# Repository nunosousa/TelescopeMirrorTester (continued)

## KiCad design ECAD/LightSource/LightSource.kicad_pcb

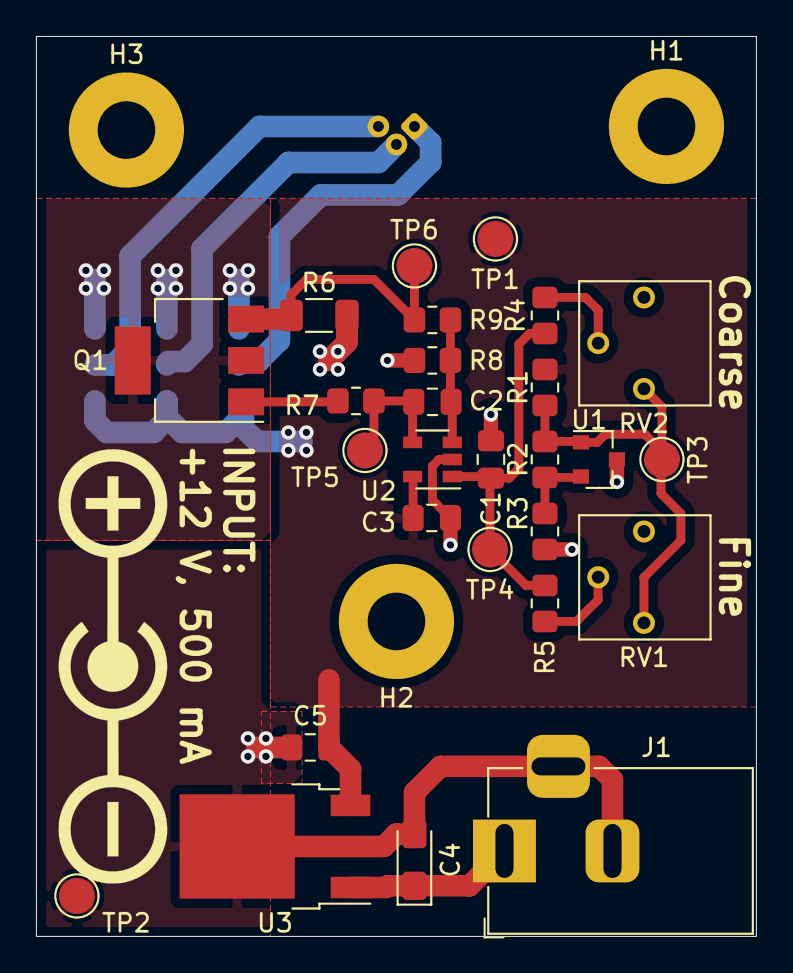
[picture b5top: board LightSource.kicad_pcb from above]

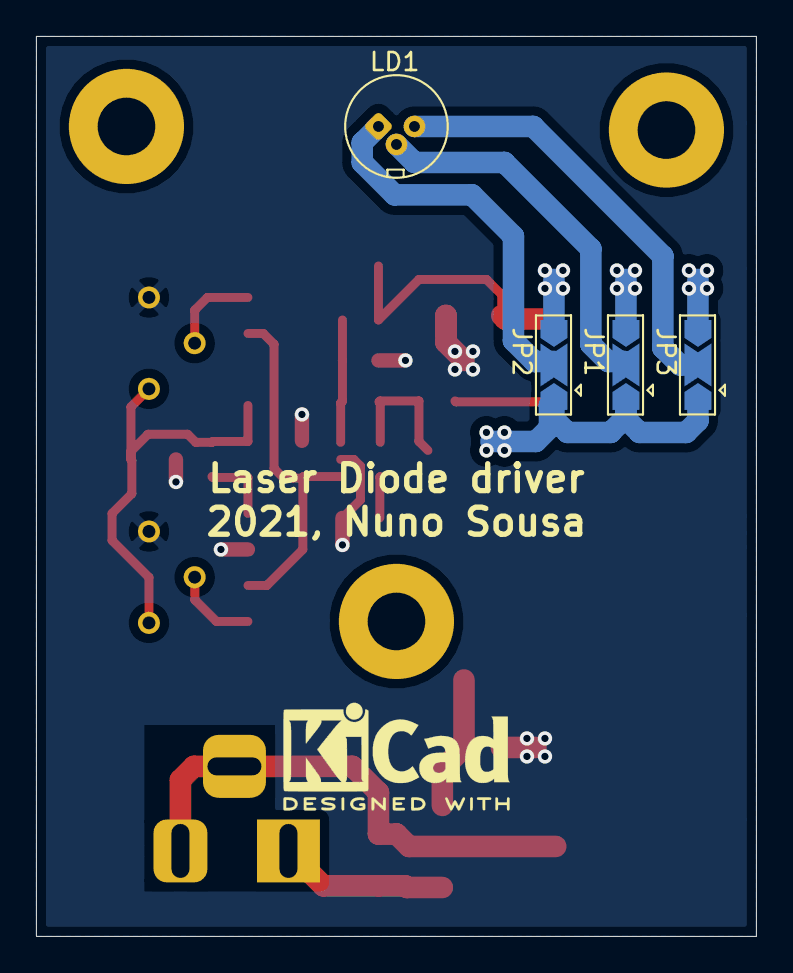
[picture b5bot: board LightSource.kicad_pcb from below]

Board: 2 copper layers, 40.0 x 50.0 mm, 34 parts (4 on the bottom side), 16 nets.

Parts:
C1: 10uC; C_0805_2012Metric_Pad1.18x1.45mm_HandSolder
C2: 100pC; C_0805_2012Metric_Pad1.18x1.45mm_HandSolder
C3, C5: 0.1uC; C_0805_2012Metric_Pad1.18x1.45mm_HandSolder
C4: 0.33uCP; CP_EIA-3216-18_Kemet-A_Pad1.58x1.35mm_HandSolder
H1, H2, H3: MountingHole; MountingHole_3.2mm_M3_Pad
J1: Barrel_Jack_Switch; BarrelJack_Horizontal
JP1, JP2, JP3: JP; SolderJumper-3_P2.0mm_Open_TrianglePad1.0x1.5mm
LD1: LD; LaserDiode_TO18-D5.6-3
Q1: FZT694BTA; SOT-223-3_TabPin2
R1: 510R; R_0805_2012Metric_Pad1.20x1.40mm_HandSolder
R2, R7: 0R; R_0805_2012Metric_Pad1.20x1.40mm_HandSolder
R3: NC; R_0805_2012Metric_Pad1.20x1.40mm_HandSolder
R4: 10kR; R_0805_2012Metric_Pad1.20x1.40mm_HandSolder
R5: 100kR; R_0805_2012Metric_Pad1.20x1.40mm_HandSolder
R6: 120R; R_1206_3216Metric_Pad1.30x1.75mm_HandSolder
R8: 15kR; R_0805_2012Metric_Pad1.20x1.40mm_HandSolder
R9: 30kR; R_0805_2012Metric_Pad1.20x1.40mm_HandSolder
RV1, RV2: 500R; Potentiometer_Bourns_3362P_Vertical
TP1, TP2, TP3, TP4, TP5, TP6: TestPoint; TestPoint_Pad_D2.0mm
U1: TL431; SOT-23
U2: LM321; SOT-23-5
U3: L78M09; TO-252-2

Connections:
+9V: C3.1, C5.1, JP1.1, JP2.1, JP3.1, R1.1, TP1.1, U2.5, U3.3
+12V: C4.1, J1.1, U3.1
/Light Source/Cathode: JP1.3, JP2.3, JP3.3, Q1.2
/Vout: R1.2, R2.1, RV1.1, RV2.1, TP3.1, U1.1
/Vref: R2.2, R3.1, U1.2
GND: C1.2, C3.2, C4.2, C5.2, J1.2, J1.3, R3.2, R6.2, R8.2, RV1.3, RV2.3, TP2.1, U1.3, U2.2, U3.2
unnamed: C1.1, R4.1, R5.1, TP4.1, U2.1
unnamed: C2.1, R7.2, TP5.1, U2.4
unnamed: C2.2, R8.1, R9.2, U2.3
unnamed: JP1.2, LD1.2
unnamed: JP2.2, LD1.1
unnamed: JP3.2, LD1.3
unnamed: Q1.1, R7.1
unnamed: Q1.3, R6.1, R9.1, TP6.1
unnamed: R4.2, RV2.2
unnamed: R5.2, RV1.2

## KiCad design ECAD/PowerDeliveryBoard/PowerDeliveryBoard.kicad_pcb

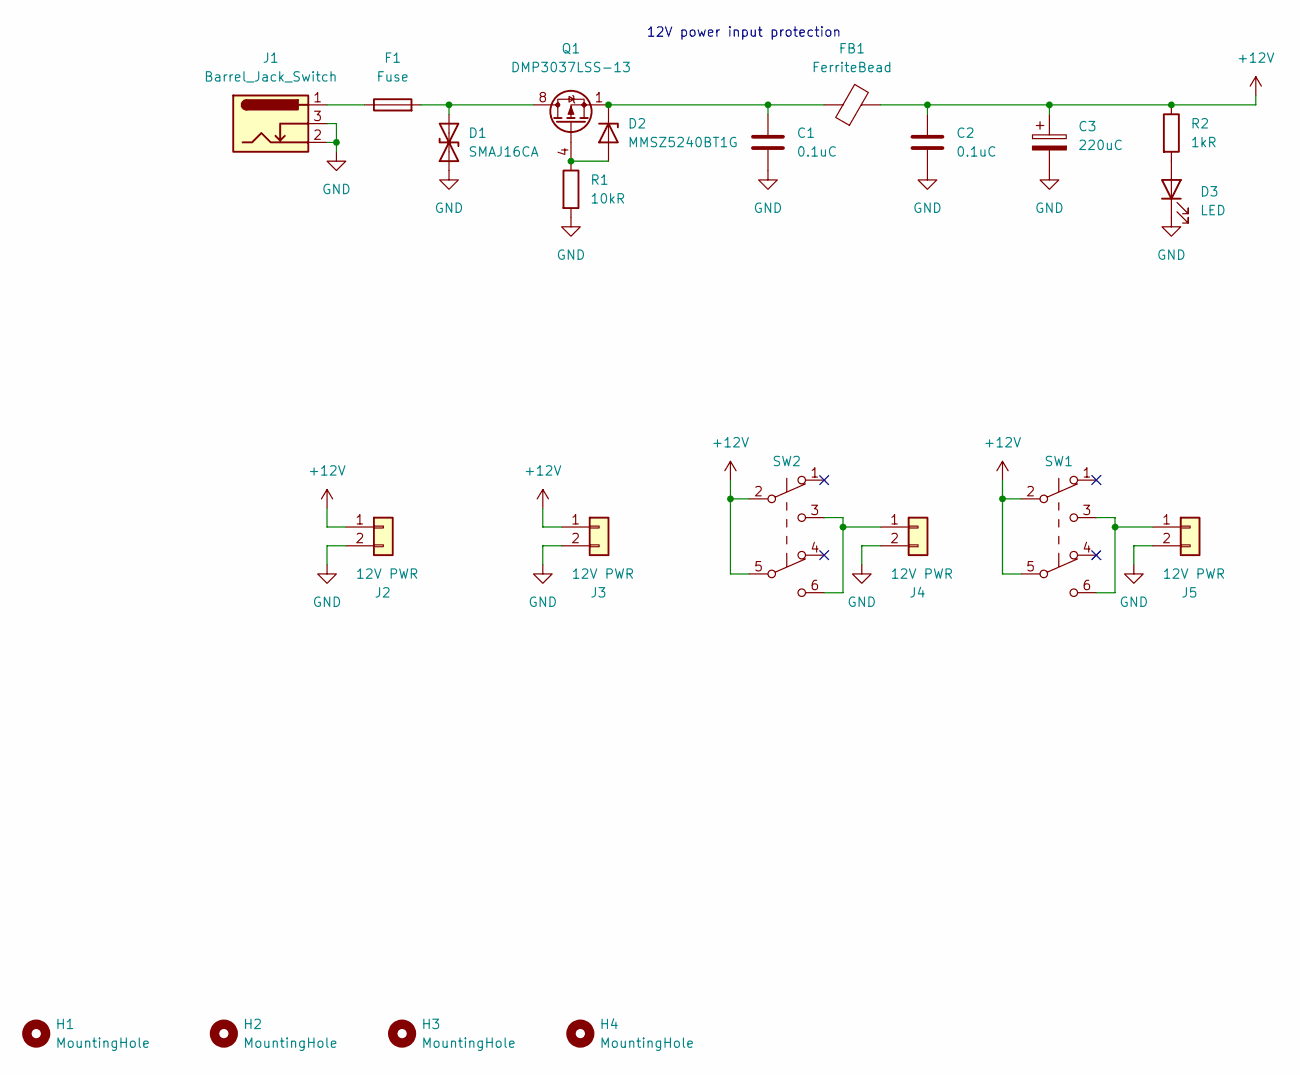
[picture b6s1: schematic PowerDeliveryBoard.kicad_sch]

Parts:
C1, C2: 0.1uC; C_0805_2012Metric_Pad1.18x1.45mm_HandSolder; MPN CL21B104KBCNNNC
C3: 220uC; CP_Radial_D8.0mm_P3.50mm; MPN 25YXF220MEFC8X11.5
D1: SMAJ16CA; D_SMA; MPN SMAJ16CA-13-F
D2: MMSZ5240BT1G; D_SOD-123; MPN MMSZ5240BT1G
D3: LED; D_0805_2012Metric_Pad1.15x1.40mm_HandSolder; MPN 17-21SYGC/S530-E3/TR8
F1: Fuse; Fuseholder_Cylinder-5x20mm_Stelvio-Kontek_PTF78_Horizontal_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; MPN PTF-77
FB1: FerriteBead; L_1806_4516Metric; MPN BLM41PG600SN1L
H1, H2, H3, H4: MountingHole; MountingHole_5.3mm_M5; MPN N/A
J1: Barrel_Jack_Switch; BarrelJack_DC-042C-W-2.5_Horizontal; MPN DC-042C-W-2.5
J2, J3, J4, J5: 12V PWR; HC-2510-2A; MPN HC-2510-2A
Q1: DMP3037LSS-13; SOIC-8_3.9x4.9mm_P1.27mm; MPN DMP3037LSS-13
R1: 10kR; R_0805_2012Metric_Pad1.20x1.40mm_HandSolder; MPN RC0805FR-0710KL
R2: 1kR; R_0805_2012Metric_Pad1.20x1.40mm_HandSolder; MPN AC0805FR-7W1KL
SW1, SW2: SW_Push_DPDT; SW_Push_2P2T_Toggle_Generic_5_8_x_5_8; MPN PB22E60L

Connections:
+12V: C2.2, C3.1, FB1.2, J2.1, J3.1, R2.1, SW1.2 (B), SW1.5 (B), SW2.2 (B), SW2.5 (B)
GND: C1.1, C2.1, C3.2, D1.1 (A1), D3.1 (K), J1.2, J1.3, J2.2, J3.2, J4.2, J5.2, R1.2
unnamed: C1.2, D2.1 (K), FB1.1, Q1.1 (S), Q1.2 (S), Q1.3 (S)
unnamed: D1.2 (A2), F1.2, Q1.5 (D), Q1.6 (D), Q1.7 (D), Q1.8 (D)
unnamed: D2.2 (A), Q1.4 (G), R1.1
unnamed: F1.1, J1.1
unnamed: J4.1, SW2.3 (C), SW2.6 (C)
unnamed: J5.1, SW1.3 (C), SW1.6 (C)
unnamed: D3.2 (A), R2.2

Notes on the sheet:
12V power input protection

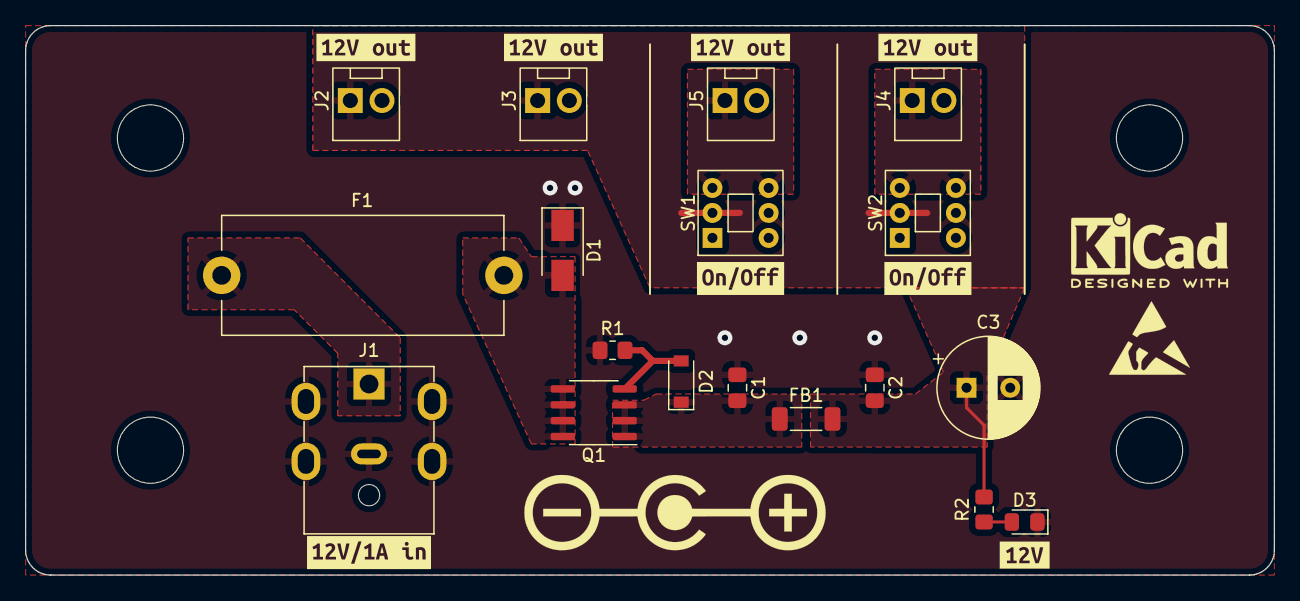
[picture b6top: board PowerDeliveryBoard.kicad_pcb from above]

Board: 2 copper layers, 100.0 x 44.0 mm, 30 parts (0 on the bottom side), 9 nets.

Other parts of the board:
kibuzzard-6388F516: G***; kibuzzard-6388F516
kibuzzard-63891CDB: G***; kibuzzard-63891CDB
kibuzzard-638910D3, kibuzzard-638910D3#2: G***; kibuzzard-638910D3
kibuzzard-638911E5: G***; kibuzzard-638911E5
kibuzzard-638911EA: G***; kibuzzard-638911EA
kibuzzard-6389104C, kibuzzard-6389104C#2: G***; kibuzzard-6389104C

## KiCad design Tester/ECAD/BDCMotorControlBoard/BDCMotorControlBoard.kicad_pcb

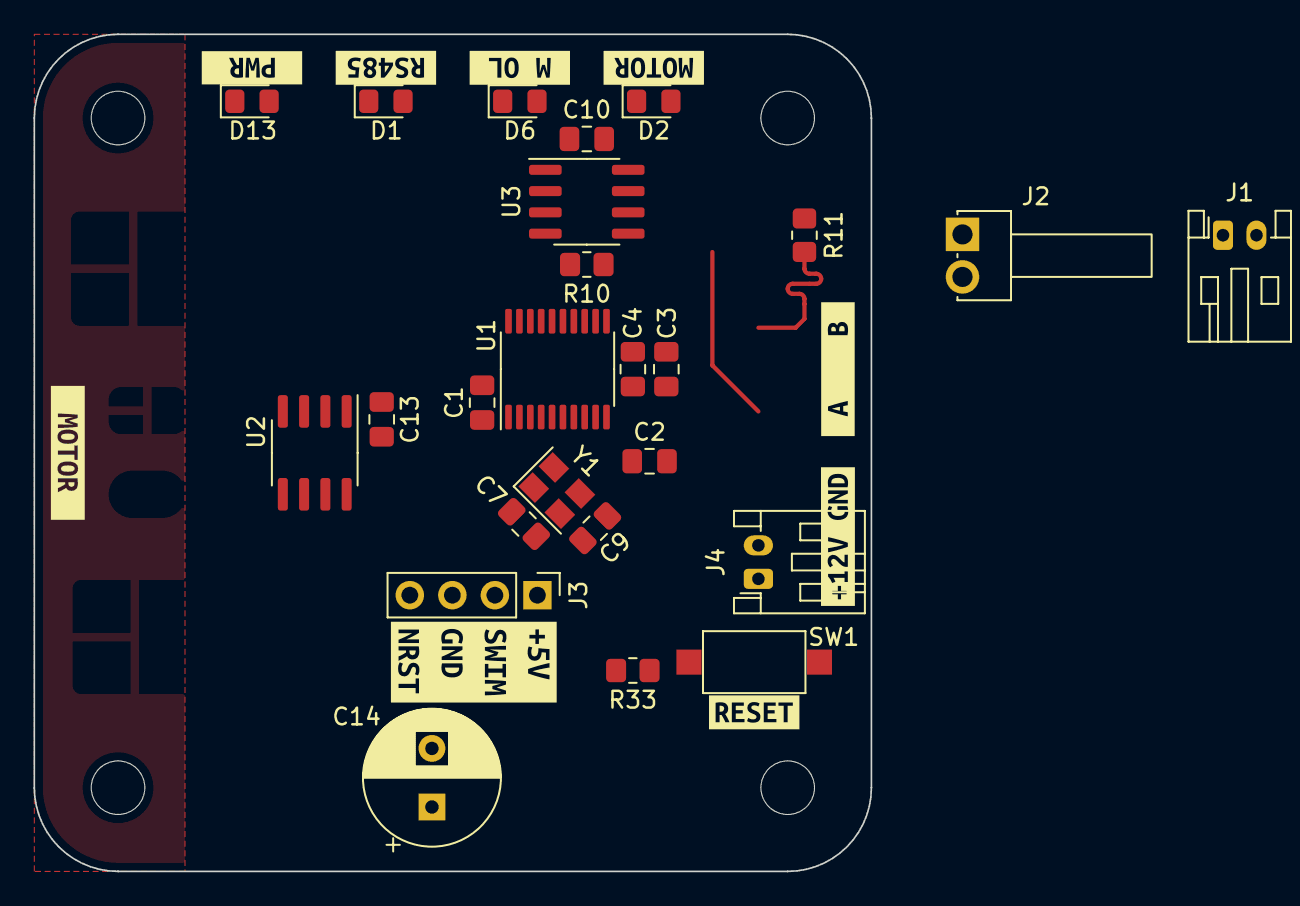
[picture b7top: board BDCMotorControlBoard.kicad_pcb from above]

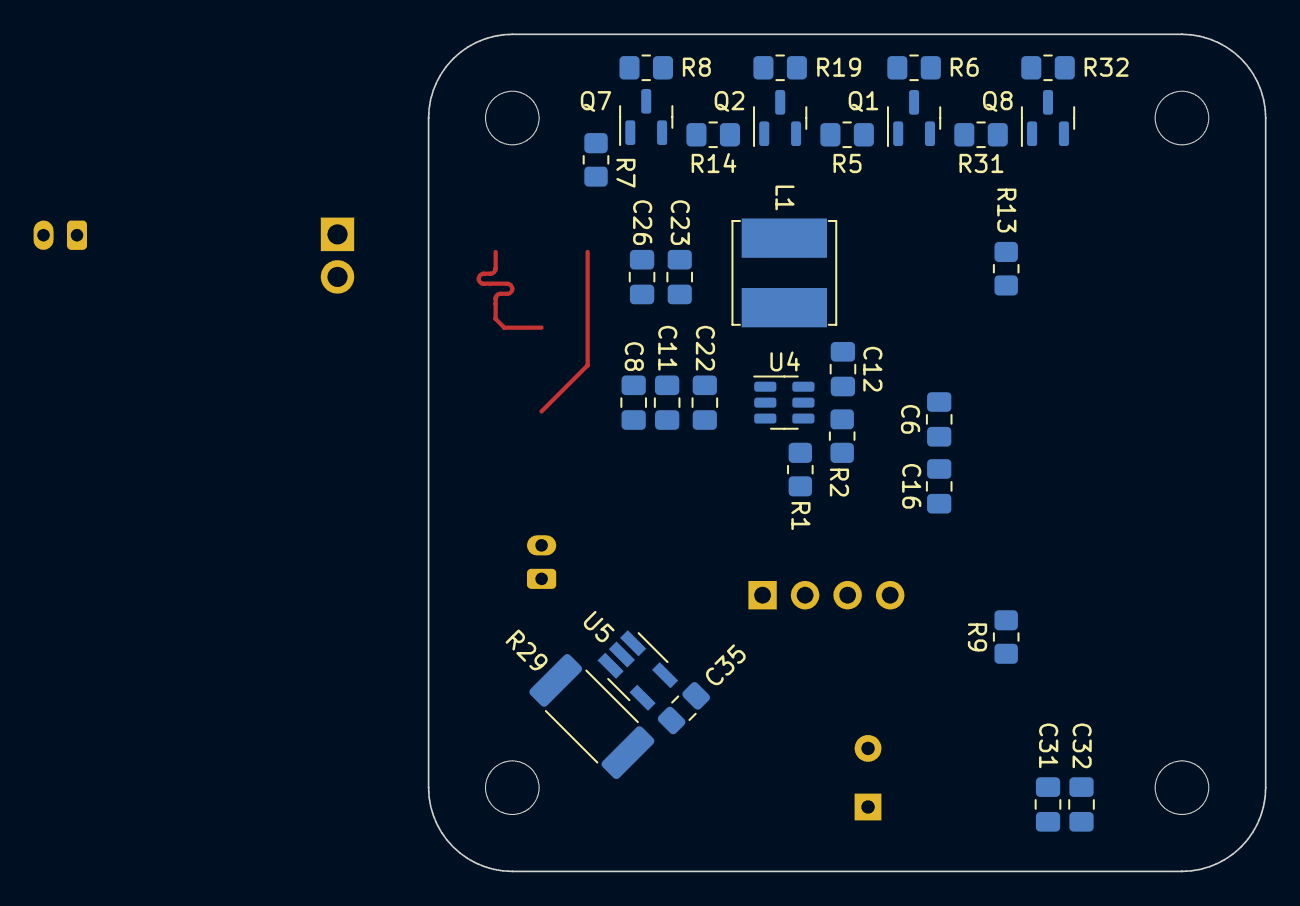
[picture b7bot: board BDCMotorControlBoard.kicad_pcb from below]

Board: 4 copper layers, 50.0 x 50.0 mm, 69 parts (31 on the bottom side), 34 nets.

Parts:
C1, C3, C10, C12, C22, C35: 0.1uC; C_0805_2012Metric_Pad1.18x1.45mm_HandSolder
C2, C4, C6, C13, C16, C31, C32: 1uC; C_0805_2012Metric_Pad1.18x1.45mm_HandSolder
C7, C9: 12pC; C_0805_2012Metric_Pad1.18x1.45mm_HandSolder
C8, C11: 10uC; C_0805_2012Metric_Pad1.18x1.45mm_HandSolder
C14: 220uC; CP_Radial_D8.0mm_P3.50mm
C23, C26: 22uC; C_0805_2012Metric_Pad1.18x1.45mm_HandSolder
D1, D2, D6, D13: LED; LED_0805_2012Metric_Pad1.15x1.40mm_HandSolder
H1, H2, H3, H4: MountingHole; MountingHole_3.2mm_M3
J1: RS485; JST_PH_S2B-PH-K_1x02_P2.00mm_Horizontal
J2: 12V PWR; HC-2510-2AW
J3: SWIM connector; PinHeader_1x04_P2.54mm_Vertical
J4: Motor; JST_PH_S2B-PH-K_1x02_P2.00mm_Horizontal
L1: 3.3uL; L_Bourns_SRN6045TA
Q1, Q2, Q7, Q8: 2N7002; SOT-23
R1, R9, R10, R13, R33: 10kR; R_0805_2012Metric_Pad1.20x1.40mm_HandSolder
R2: 54.9kR; R_0805_2012Metric_Pad1.20x1.40mm_HandSolder
R5, R7, R14, R31: 10R; R_0805_2012Metric_Pad1.20x1.40mm_HandSolder
R6, R8, R19, R32: 150R; R_0805_2012Metric_Pad1.20x1.40mm_HandSolder
R11: 120R; R_0805_2012Metric_Pad1.20x1.40mm_HandSolder
R29: 20mR; R_2512_6332Metric_Pad1.40x3.35mm_HandSolder
SW1: SW_Push; SW_SPST_CK_RS282G05A3
U1: STM8S003F3P6; TSSOP-20_4.4x6.5mm_P0.65mm
U2: ZXBM5210-S; SOIC-8_3.9x4.9mm_P1.27mm
U3: SP485; SOIC-8_3.9x4.9mm_P1.27mm
U4: TPS563201; SOT-23-6
U5: INA180A2; SOT-23-5_HandSoldering
Y1: Crystal_GND24; Crystal_SMD_3225-4Pin_3.2x2.5mm
kibuzzard-633AA34D: G***; kibuzzard-633AA34D
kibuzzard-634C1717: G***; kibuzzard-634C1717
kibuzzard-6349C15E: G***; kibuzzard-6349C15E
kibuzzard-6349C16E: G***; kibuzzard-6349C16E
kibuzzard-6349C164: G***; kibuzzard-6349C164
kibuzzard-6349C168: G***; kibuzzard-6349C168
kibuzzard-63377EA3: G***; kibuzzard-63377EA3
kibuzzard-63377ED3: G***; kibuzzard-63377ED3
kibuzzard-633802D7: G***; kibuzzard-633802D7

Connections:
+5V: C3.1, C4.1, C10.1, C23.1, C26.1, C35.1, J3.1, L1.2, R2.2, R6.1, R8.1, R19.1, R32.1, R33.1, U1.9 (VDD), U3.8 (VCC), U5.5 (V+)
+12V: C8.1, C11.1, C22.1, J2.1, R29.1, U4.3 (VIN), U4.5 (EN), U5.3 (+)
/A_Meas: U1.19 (PD2), U5.1
/H-bridge/Top_Rail: C6.1, C14.1, C16.1, C31.1, C32.1, R9.1, R29.2, U5.4 (-)
/M_ACT_LED: R7.1, U1.17 (PC7)
/NRST: C1.1, J3.4, R33.2, SW1.1, U1.4 (NRST)
/OC_LED: R14.1, U1.12 (PB4)
/OSCIN: C7.1, U1.5 (PA1), Y1.1
/OSCOUT: C9.1, U1.6 (PA2), Y1.3
/PWR_LED: R31.1, U1.10 (PA3)
/RS485_DI: U1.2 (PD5), U3.4 (DI)
/RS485_LED: R5.1, U1.20 (PD3)
/RS485_RO: U1.3 (PD6), U3.1 (RO)
/RS485_TX: R10.1, U1.1 (PD4), U3.2 (~RE), U3.3 (DE)
/SWIM: J3.2, U1.18 (PD1)
GND: C1.2, C2.2, C3.2, C4.2, C6.2, C7.2, C8.2, C9.2, C10.2, C11.2, C13.2, C14.2, C16.2, C22.2, C23.2, C26.2, C31.2, C32.2, C35.2, J2.2, J3.3, Q1.2 (S), Q2.2 (S), Q7.2 (S), Q8.2 (S), R1.2, R10.2, R13.2, SW1.2, U1.7 (VSS), U3.5 (GND), U4.1 (GND), U5.2 (GND), Y1.2, Y1.4
unnamed: C2.1, U1.8 (VCAP)
unnamed: C12.1, U4.6 (VBST)
unnamed: C12.2, L1.1, U4.2 (SW)
unnamed: D1.1 (K), Q1.3 (D)
unnamed: D1.2 (A), R6.2
unnamed: D2.1 (K), Q7.3 (D)
unnamed: D2.2 (A), R8.2
unnamed: D6.1 (K), Q2.3 (D)
unnamed: D6.2 (A), R19.2
unnamed: D13.1 (K), Q8.3 (D)
unnamed: D13.2 (A), R32.2
unnamed: J1.1, R11.1, U3.7 (B)
unnamed: J1.2, R11.2, U3.6 (A)
unnamed: Q1.1 (G), R5.2
unnamed: Q2.1 (G), R14.2
unnamed: Q7.1 (G), R7.2
unnamed: Q8.1 (G), R31.2
unnamed: R1.1, R2.1, U4.4 (VFB)

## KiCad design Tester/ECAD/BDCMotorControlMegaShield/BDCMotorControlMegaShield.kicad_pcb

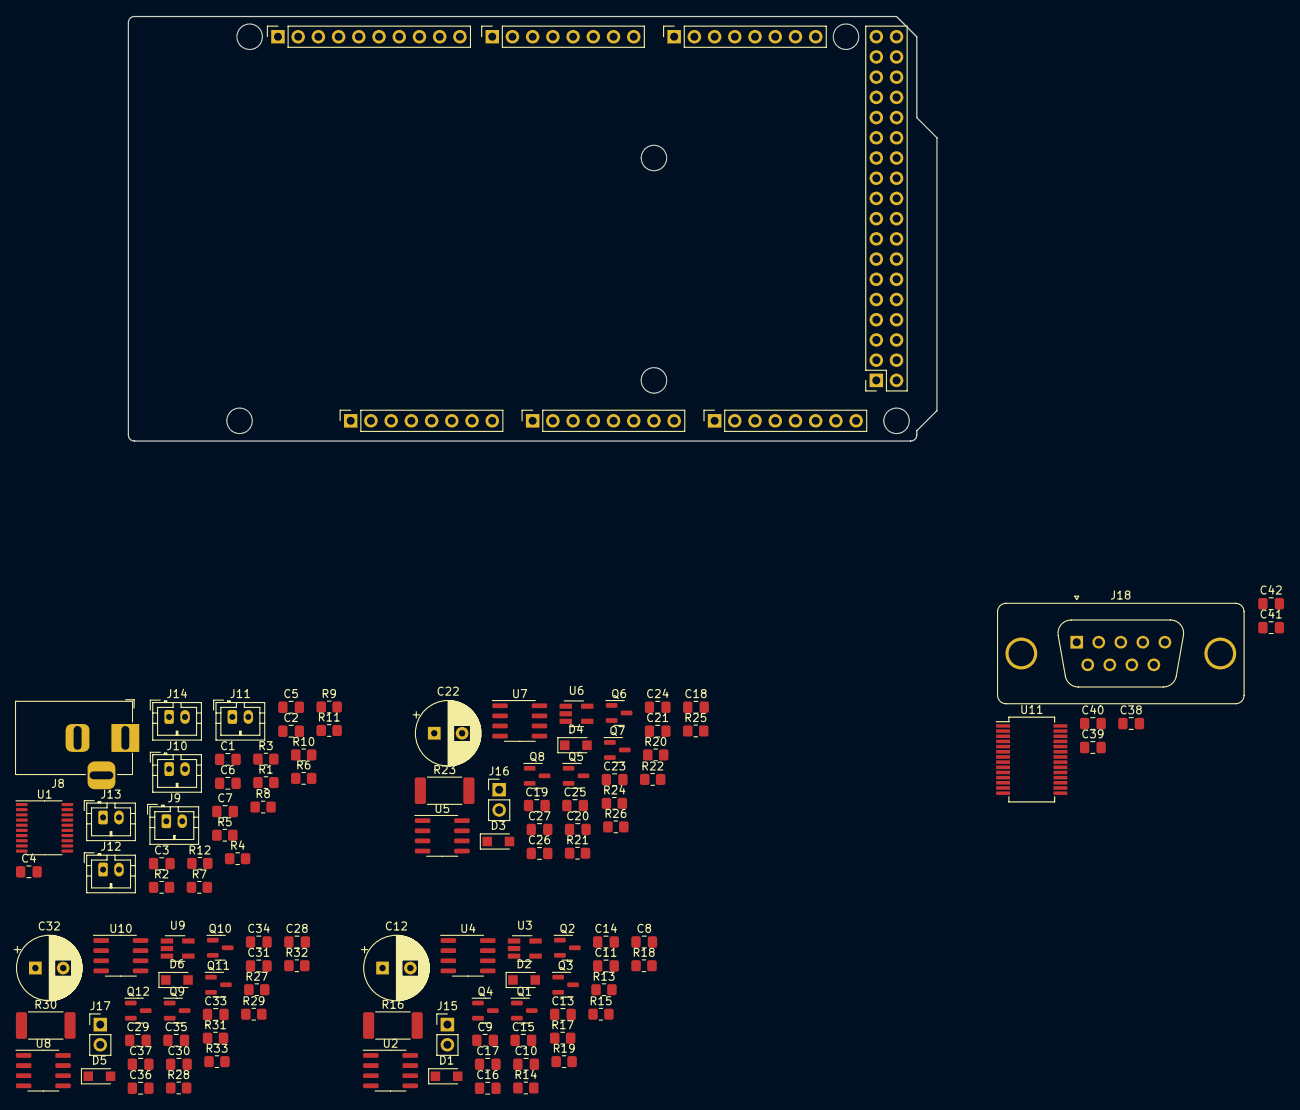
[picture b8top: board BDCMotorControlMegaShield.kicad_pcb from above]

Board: 2 copper layers, 101.6 x 53.3 mm, 128 parts (0 on the bottom side), 86 nets, no tracks yet.

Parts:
C1, C2, C3, C4, C5, C6, C9, C15, C16, C19, C25, C26, C29, C35, C36, C38, C39, C40, C41, C42: 0.1uC; C_0805_2012Metric_Pad1.18x1.45mm_HandSolder
C7, C8, C10, C11, C13, C14, C17, C18, C20, C21, C23, C24, C27, C28, C30, C31, C33, C34, C37: 1uC; C_0805_2012Metric_Pad1.18x1.45mm_HandSolder
C12, C22, C32: 220uC; CP_Radial_D8.0mm_P3.50mm
D1, D2, D3, D4, D5, D6: PMEG6010ER; Nexperia_CFP3_SOD-123W
J1: Power; PinSocket_1x08_P2.54mm_Vertical
J2: PWM; PinSocket_1x10_P2.54mm_Vertical
J3, J5: Analog; PinSocket_1x08_P2.54mm_Vertical
J4: PWM; PinSocket_1x08_P2.54mm_Vertical
J6: Communication; PinSocket_1x08_P2.54mm_Vertical
J7: Digital; PinSocket_2x18_P2.54mm_Vertical
J8: Barrel_Jack_Switch; BarrelJack_Horizontal
J9, J10: SW0 switch; JST_PH_B2B-PH-K_1x02_P2.00mm_Vertical
J11, J12, J13, J14: SW1 switch; JST_PH_B2B-PH-K_1x02_P2.00mm_Vertical
J15, J16, J17: Motor connector; PinHeader_1x02_P2.54mm_Vertical
J18: DB9_Male; DSUB-9_Male_Vertical_P2.77x2.84mm_MountingHoles
MH1, MH2, MH3, MH4, MH5, MH6: MountingHole_3.2mm
Q1, Q2, Q3, Q4, Q5, Q6, Q7, Q8, Q9, Q10, Q11, Q12: Q_NMOS_GSD; SOT-23
R1, R2, R3, R4, R5, R6, R7, R8, R9, R10, R11, R12: 10kR; R_0805_2012Metric_Pad1.20x1.40mm_HandSolder
R13, R14, R15, R17, R18, R19, R20, R21, R22, R24, R25, R26, R27, R28, R29, R31, R32, R33: 10R; R_0805_2012Metric_Pad1.20x1.40mm_HandSolder
R16, R23, R30: 20mR; R_2512_6332Metric_Pad1.40x3.35mm_HandSolder
U1: 74HC7541; TSSOP-20_4.4x6.5mm_P0.65mm
U2, U4, U5, U7, U8, U10: IR2103; SOIC-8_3.9x4.9mm_P1.27mm
U3, U6, U9: INA180A2; SOT-23-5_HandSoldering
U11: SP213E; SSOP-28_5.3x10.2mm_P0.65mm

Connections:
+5V: C7.1, C16.1, C26.1, C36.1, J1.5, J7.35, J7.36, R1.1, R2.1, R3.1, R4.1, R5.1, R6.1, U1.20 (VCC), U3.5 (V+), U6.5 (V+), U9.5 (V+)
+12V: J8.1, R16.2, R23.2, R30.2, U3.3 (+), U6.3 (+), U9.3 (+)
/*3: J4.5, U2.2 (HIN), U2.3 (~LIN)
/*5: J4.3, U4.2 (HIN), U4.3 (~LIN)
/*6: J4.2, U5.2 (HIN), U5.3 (~LIN)
/*9: J2.9, U7.2 (HIN), U7.3 (~LIN)
/*10: J2.8, U8.2 (HIN), U8.3 (~LIN)
/*11: J2.7, U10.2 (HIN), U10.3 (~LIN)
/A0: J3.1, U3.1
/A1: J3.2, U6.1
/A2: J3.3, U9.1
/H-bridge #1/Motor_L: C9.2, J15.2, Q1.2 (S), Q2.3 (D), U2.6 (VS)
/H-bridge #1/Motor_R: C15.2, J15.1, Q3.2 (S), Q4.3 (D), U4.6 (VS)
/H-bridge #2/Motor_L: C19.2, J16.2, Q5.2 (S), Q6.3 (D), U5.6 (VS)
/H-bridge #2/Motor_R: C25.2, J16.1, Q7.2 (S), Q8.3 (D), U7.6 (VS)
/H-bridge #3/Motor_L: C29.2, J17.2, Q9.2 (S), Q10.3 (D), U8.6 (VS)
/H-bridge #3/Motor_R: C35.2, J17.1, Q11.2 (S), Q12.3 (D), U10.6 (VS)
/RS-232/C1+: C38.2, U11.12 (C1+)
/RS-232/C1-: C38.1, U11.14 (C1-)
/RS-232/C2+: C40.2, U11.15 (C2+)
/RS-232/C2-: C40.1, U11.16 (C2-)
/RS-232/CTS: J18.8, U11.4 (RIN2)
/RS-232/DCD: J18.1, U11.18 (RIN5)
/RS-232/DSR: J18.6, U11.27 (RIN3)
/RS-232/DTR: J18.4, U11.3 (DOUT2)
/RS-232/RI: J18.9, U11.23 (RIN4)
/RS-232/RTS: J18.7, U11.1 (DOUT3)
/RS-232/RX: J18.2, U11.9 (RIN1)
/RS-232/TX: J18.3, U11.2 (DOUT1)
/RS-232/V+: C41.1, U11.13 (V+)
/RS-232/V-: C39.2, U11.17 (V-)
/SCL/21: J2.1, J6.8
/SDA/20: J2.2, J6.7
/SW00: C1.1, R7.2, U1.2 (A0)
/SW01: C2.1, R8.2, U1.3 (A1)
/SW10: C3.1, R9.2, U1.4 (A2)
/SW11: C4.1, R10.2, U1.5 (A3)
/SW20: C5.1, R11.2, U1.6 (A4)
/SW21: C6.1, R12.2, U1.7 (A5)
GND: C1.2, C2.2, C3.2, C4.2, C5.2, C6.2, C7.2, C8.2, C10.2, C11.2, C12.2, C13.2, C14.2, C16.2, C17.2, C18.2, C20.2, C21.2, C22.2, C23.2, C24.2, C26.2, C27.2, C28.2, C30.2, C31.2, C32.2, C33.2, C34.2, C36.2, C37.2, C39.1, C42.1, J1.6, J1.7, J2.4, J7.1, J7.2, J8.2, J8.3, J9.1, J10.1, J11.1, J12.1, J13.1, J14.1, J18.5, Q2.2 (S), Q4.2 (S), Q6.2 (S), Q8.2 (S), Q10.2 (S), Q12.2 (S), U1.1 (G1), U1.8 (A6), U1.9 (A7), U1.10 (GND), U1.19 (G2), U2.4 (COM), U3.2 (GND), U4.4 (COM), U5.4 (COM), U6.2 (GND), U7.4 (COM), U8.4 (COM), U9.2 (GND), U10.4 (COM), U11.10 (GND)
unnamed: C9.1, D1.1 (K), U2.8 (VB)
unnamed: C8.1, C10.1, C11.1, C12.1, C13.1, C14.1, C17.1, Q1.3 (D), Q3.3 (D), R13.1, R16.1, R19.1, U2.1 (VCC), U3.4 (-), U4.1 (VCC)
unnamed: C15.1, D2.1 (K), U4.8 (VB)
unnamed: C18.1, C20.1, C21.1, C22.1, C23.1, C24.1, C27.1, Q5.3 (D), Q7.3 (D), R20.1, R23.1, R26.1, U5.1 (VCC), U6.4 (-), U7.1 (VCC)
unnamed: C19.1, D3.1 (K), U5.8 (VB)
unnamed: C25.1, D4.1 (K), U7.8 (VB)
unnamed: C28.1, C30.1, C31.1, C32.1, C33.1, C34.1, C37.1, Q9.3 (D), Q11.3 (D), R27.1, R30.1, R33.1, U8.1 (VCC), U9.4 (-), U10.1 (VCC)
unnamed: C29.1, D5.1 (K), U8.8 (VB)
unnamed: C35.1, D6.1 (K), U10.8 (VB)
unnamed: D1.2 (A), R13.2
unnamed: D2.2 (A), R19.2
unnamed: D3.2 (A), R20.2
unnamed: D4.2 (A), R26.2
unnamed: D5.2 (A), R27.2
unnamed: D6.2 (A), R33.2
unnamed: J9.2, R1.2, R7.1
unnamed: J10.2, R2.2, R8.1
unnamed: J11.2, R3.2, R9.1
unnamed: J12.2, R4.2, R10.1
unnamed: J13.2, R5.2, R11.1
unnamed: J14.2, R6.2, R12.1
unnamed: Q1.1 (G), R14.2
unnamed: Q2.1 (G), R15.2
unnamed: Q3.1 (G), R17.1
unnamed: Q4.1 (G), R18.1
unnamed: Q5.1 (G), R21.2
unnamed: Q6.1 (G), R22.2
unnamed: Q7.1 (G), R24.1
unnamed: Q8.1 (G), R25.1
unnamed: Q9.1 (G), R28.2
unnamed: Q10.1 (G), R29.2
unnamed: Q11.1 (G), R31.1
unnamed: Q12.1 (G), R32.1
unnamed: R14.1, U2.7 (HO)
unnamed: R15.1, U2.5 (LO)
unnamed: R17.2, U4.7 (HO)
unnamed: R18.2, U4.5 (LO)
unnamed: R21.1, U5.7 (HO)
unnamed: R22.1, U5.5 (LO)
unnamed: R24.2, U7.7 (HO)
unnamed: R25.2, U7.5 (LO)
unnamed: R28.1, U8.7 (HO)
unnamed: R29.1, U8.5 (LO)
unnamed: R31.2, U10.7 (HO)
unnamed: R32.2, U10.5 (LO)
VBUS: C41.2, C42.2
